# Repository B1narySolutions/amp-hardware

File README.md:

# Amp hardware

The circuit board for our capstone guitar amp, designed in KiCad 10.

The amp board (top, then bottom seen from below):

## The amp board

One 4-layer, 100 × 78 mm board, in `amp-board/`. It holds the Daisy Seed3 that does the audio processing, the guitar and
AUX inputs, an I2C headphone amp (TPA6130A2), the battery input, the 5 V distribution and the class D speaker amp
(TPA3118D2). The Daisy stands upright in the middle and divides the board: audio on its left and in front of it, the
battery entry and class D amp on its right, all over a solid ground plane. The 5 V buck stays off the board. JLCPCB
assembles the surface-mount parts; the rest is soldered by hand from a DigiKey order.

Status: laid out, not ordered. `amp-board/DESIGN.md` lists what is still open.

## Where to look

- `amp-board/DESIGN.md`: how the board works and why, the decisions made, and what is still open
- `amp-board/TEST_PLAN.md`: bring-up and test steps
- `amp-board/amp-board.kicad_pro`: the KiCad project. Part numbers (DigiKey, LCSC) are fields on the schematic's
  parts; the order files are generated from them into `amp-board/fab/`, which git ignores
- Each ordered revision is a git tag (`amp-board-v1`, ...) with its Gerbers, assembly files and DigiKey order attached
  to the GitHub release

## Legacy boards

`legacy/` holds the two boards the amp board grew out of, kept as they were ordered on 2026-11-05: the audio board rev 2
(`legacy/audio-board/`, 2-layer, hand-soldered) and the power board rev 1 (`legacy/power-board/`), joined by screw
terminals and wires. `legacy/README.md` lists their files. They are no longer developed.

## Opening the design

Open `amp-board/amp-board.kicad_pro` with KiCad 10. The board's own footprints, symbols and 3D models are in
`amp-board/lib/`, and the library tables point to them, so no setup is needed.

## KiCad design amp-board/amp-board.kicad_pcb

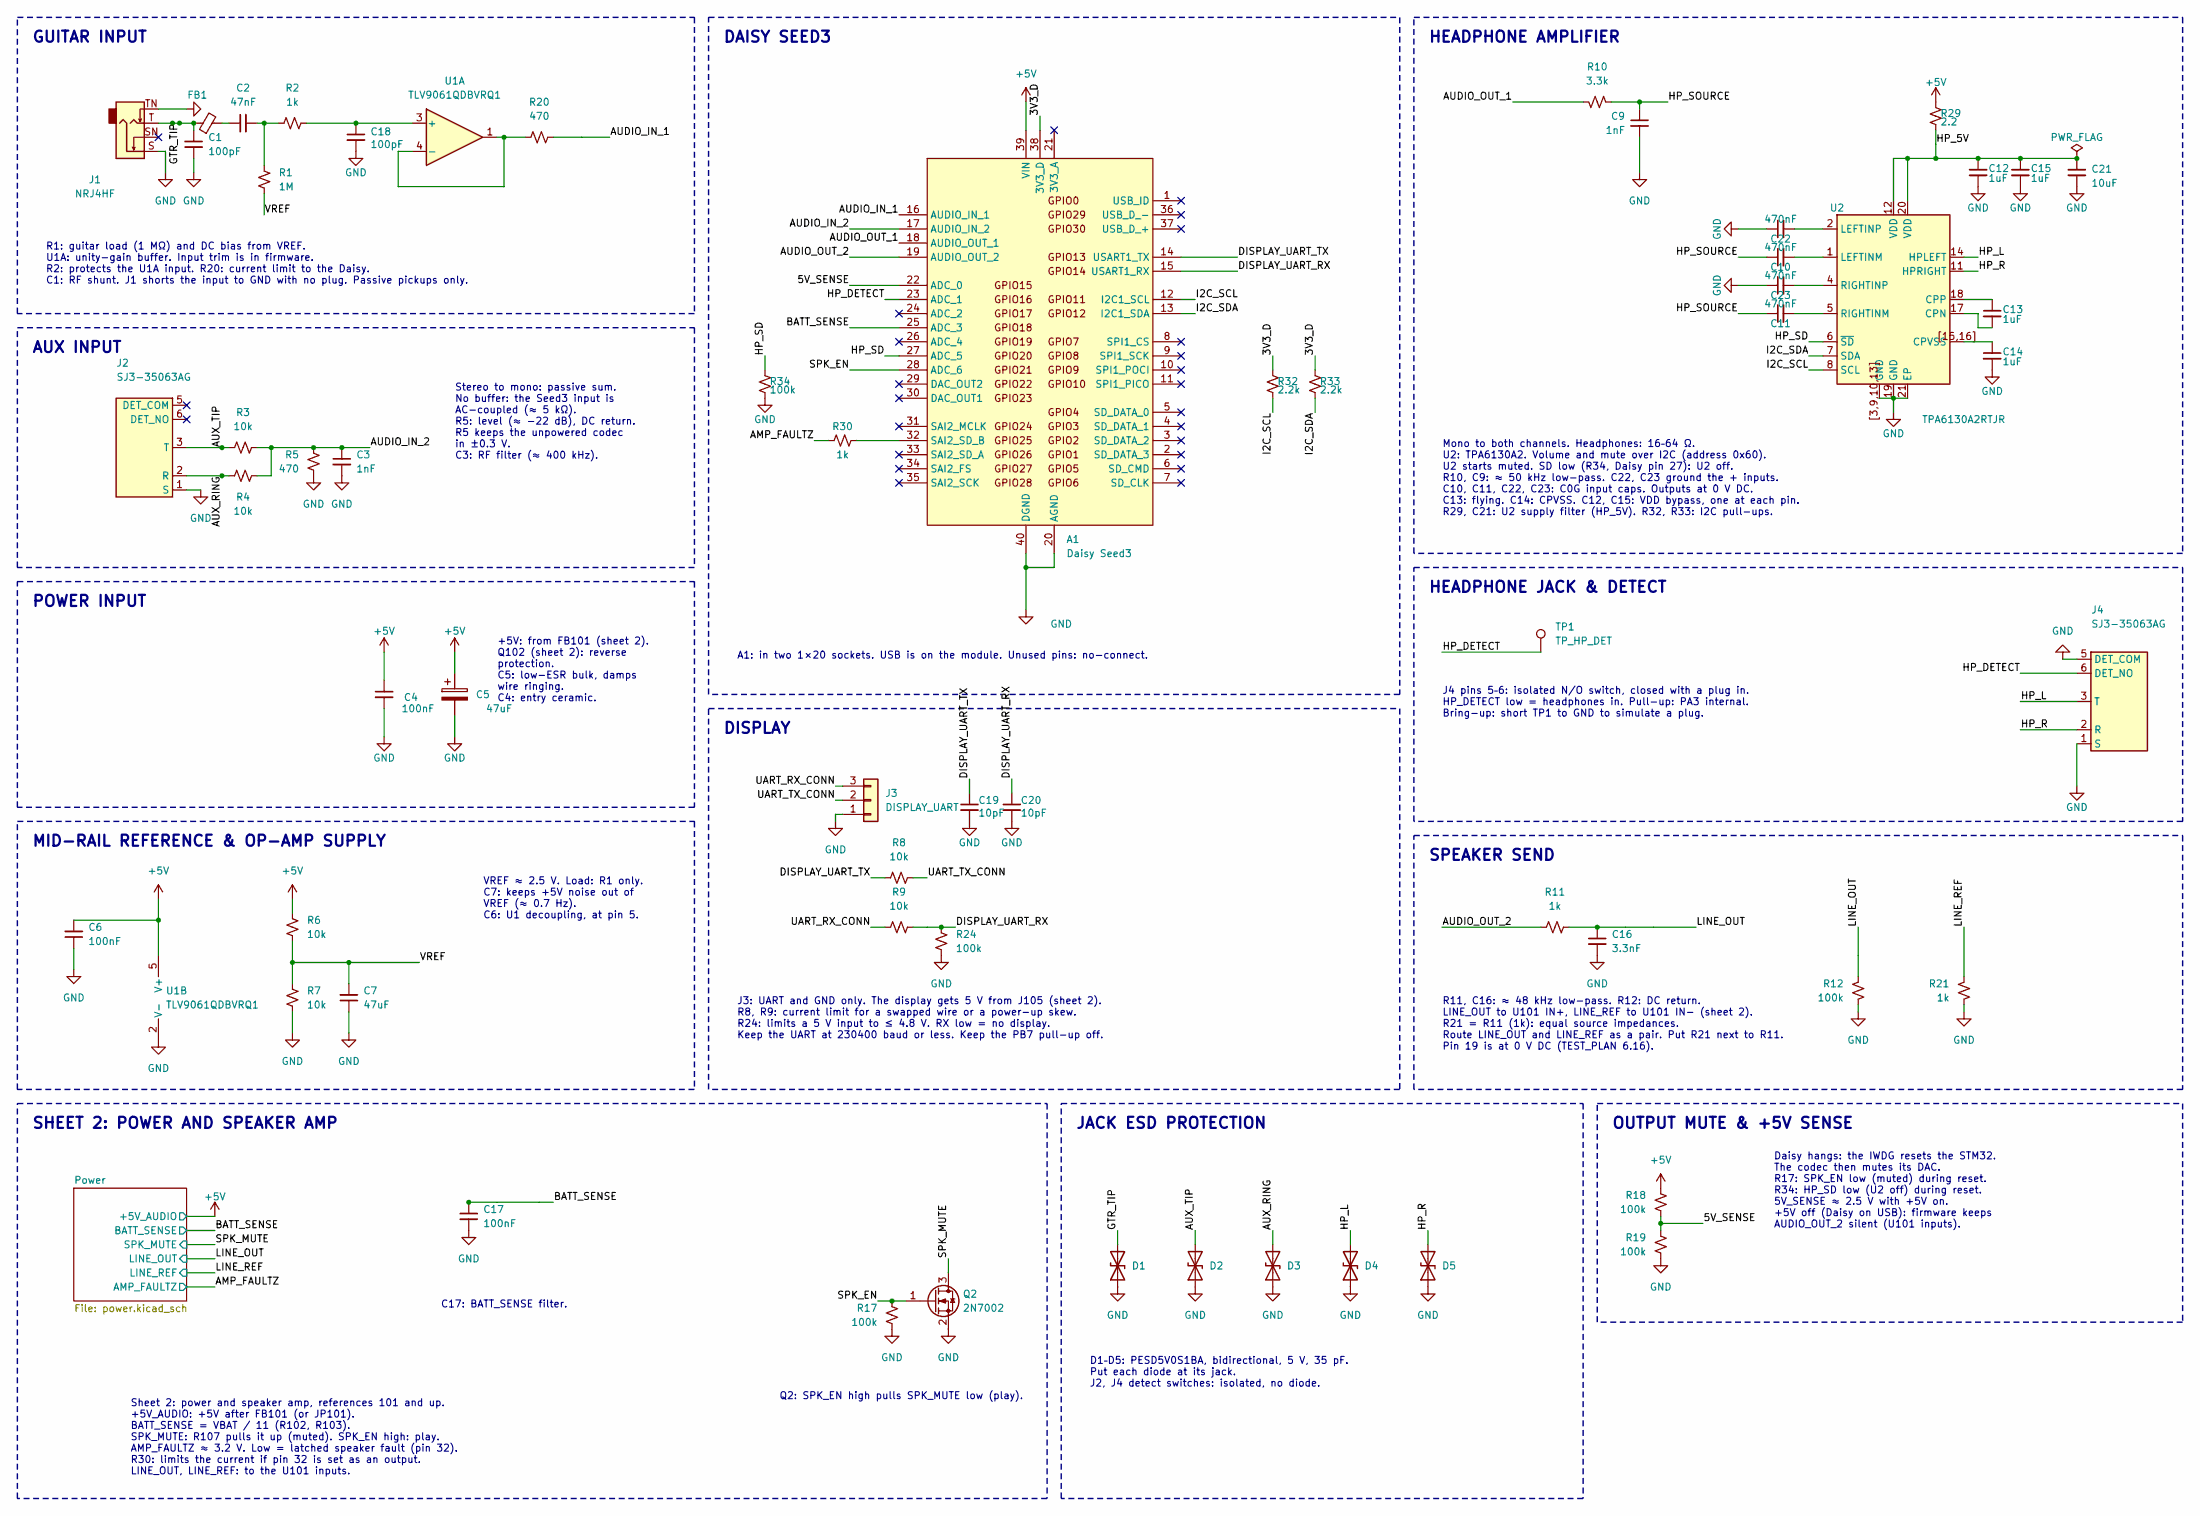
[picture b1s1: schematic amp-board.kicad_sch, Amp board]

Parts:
A1: Daisy Seed3; Electrosmith_Daisy_Seed
C1, C18: 100pF; C_0603_1608Metric; Voltage 50V; MPN CL10C101JB8NNNC; DigiKey 1276-1008-1-ND
C2: 47nF; C_0805_2012Metric; Voltage 25V; MPN C0805C473J3GACTU; DigiKey 399-C0805C473J3GACTUCT-ND
C3, C9: 1nF; C_0603_1608Metric; Voltage 50V; MPN CL10C102JB8NNNC; DigiKey 1276-1091-1-ND
C4, C6, C17: 100nF; C_0603_1608Metric; Voltage 50V; MPN C0603C104K5RACTU; DigiKey 399-C0603C104K5RACTUCT-ND
C5: 47uF; CP_Radial_D5.0mm_P2.00mm; Voltage 16V; MPN 860010472005; DigiKey 732-8628-1-ND
C7: 47uF; C_1210_3225Metric; Voltage 16V; MPN GRM32ER61C476KE15L; DigiKey 490-6539-1-ND
C10, C11, C22, C23: 470nF; C_1206_3216Metric; Voltage 25V; MPN GRM31C5C1E474JE01L; DigiKey 490-GRM31C5C1E474JE01LCT-ND
C12, C13, C14, C15: 1uF; C_0805_2012Metric; Voltage 50V; MPN C0805C105K5RACTU; DigiKey 399-C0805C105K5RACTUCT-ND
C16: 3.3nF; C_0603_1608Metric; Voltage 50V; MPN C0603C332J5GACTU; DigiKey 399-C0603C332J5GACTUCT-ND
C19, C20: 10pF; C_0603_1608Metric; Voltage 50V; MPN CL10C100JB8NNNC; DigiKey 1276-1027-1-ND
C21: 10uF; C_0805_2012Metric; Voltage 16V; MPN KGM21AR71C106KU; DigiKey 478-KGM21AR71C106KUCT-ND
D1, D2, D3, D4, D5: PESD5V0S1BA; D_SOD-323; MPN PESD5V0S1BAF; DigiKey 1727-PESD5V0S1BAFCT-ND
FB1: 600R GHz; L_0603_1608Metric; MPN BLM18HG601SN1D; DigiKey 490-1033-1-ND
J1: NRJ4HF; Jack_6.35mm_Neutrik_NRJ4HF_Horizontal; MPN NRJ4HF; DigiKey 6473-NRJ4HF-ND
J2, J4: SJ3-35063AG; Jack_3.5mm_SameSky_SJ3-35063AG_Horizontal; MPN SJ3-35063AG; DigiKey 2223-SJ3-35063AG-ND
J3: DISPLAY_UART; TerminalBlock_Phoenix_PT-1,5-3-3.5-H_1x03_P3.50mm_Horizontal; MPN 1984620; DigiKey 277-1722-ND
Q2: 2N7002; SOT-23; MPN 2N7002NXAKR; DigiKey 1727-8643-1-ND
R1: 1M; R_0603_1608Metric; MPN RC0603FR-071ML; DigiKey 311-1.00MHRCT-ND
R2, R11, R21, R30: 1k; R_0603_1608Metric; MPN RC0603FR-071KL; DigiKey 311-1.00KHRCT-ND
R3, R4, R6, R7, R8, R9: 10k; R_0603_1608Metric; MPN RMCF0603FT10K0; DigiKey RMCF0603FT10K0CT-ND
R5, R20: 470; R_0603_1608Metric; MPN RC0603FR-07470RL; DigiKey 311-470HRCT-ND
R10: 3.3k; R_0603_1608Metric; MPN RC0603FR-073K3L; DigiKey 311-3.30KHRCT-ND
R12, R17, R18, R19, R24, R34: 100k; R_0603_1608Metric; MPN RMCF0603FT100K; DigiKey RMCF0603FT100KCT-ND
R29: 2.2; R_0603_1608Metric; MPN RMCF0603FT2R20; DigiKey RMCF0603FT2R20CT-ND
R32, R33: 2.2k; R_0603_1608Metric; MPN RC0603FR-072K2L; DigiKey 311-2.20KHRCT-ND
TP1: TP_HP_DET; TestPoint_Pad_D2.0mm
U1: TLV9061QDBVRQ1; SOT-23-5; MPN TLV9061QDBVRQ1; DigiKey 296-TLV9061QDBVRQ1CT-ND
U2: TPA6130A2RTJR; WQFN-20-1EP_4x4mm_P0.5mm_EP2.7x2.7mm; MPN TPA6130A2RTJR; DigiKey 296-21656-1-ND

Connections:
+5V: A1.39 (VIN), C4.1, C5.1, C6.2, R6.1, R18.1, R29.1, U1.5 (V+); also elsewhere on the board
/3V3_D: A1.38 (3V3_D), R32.1, R33.1
/5V_SENSE: A1.22 (ADC_0), R18.2, R19.1
/AMP_FAULTZ: R30.1; also elsewhere on the board
/AUDIO_IN_1: A1.16 (AUDIO_IN_1), R20.2
/AUDIO_IN_2: A1.17 (AUDIO_IN_2), C3.1, R3.2, R4.2, R5.1
/AUDIO_OUT_1: A1.18 (AUDIO_OUT_1), R10.2
/AUDIO_OUT_2: A1.19 (AUDIO_OUT_2), R11.1
/AUX_RING: D3.2 (A2), J2.2 (R), R4.1
/AUX_TIP: D2.2 (A2), J2.3 (T), R3.1
/BATT_SENSE: A1.25 (ADC_3), C17.1; also elsewhere on the board
/DISPLAY_UART_RX: A1.15 (USART1_RX), C20.1, R9.2, R24.1
/DISPLAY_UART_TX: A1.14 (USART1_TX), C19.1, R8.1
/GTR_TIP: C1.1, D1.2 (A2), FB1.1, J1.T
/HP_5V: C12.1, C15.1, C21.1, R29.2, U2.12 (VDD), U2.20 (VDD)
/HP_DETECT: A1.23 (ADC_1), J4.6 (DET_NO), TP1.1 (1_1)
/HP_L: D4.2 (A2), J4.3 (T), U2.14 (HPLEFT)
/HP_R: D5.2 (A2), J4.2 (R), U2.11 (HPRIGHT)
/HP_SD: A1.27 (ADC_5), R34.1, U2.6 (~SD)
/HP_SOURCE: C9.1, C10.1, C11.1, R10.1
/I2C_SCL: A1.12 (I2C1_SCL), R32.2, U2.8 (SCL)
/I2C_SDA: A1.13 (I2C1_SDA), R33.2, U2.7 (SDA)
/LINE_OUT: C16.1, R11.2, R12.2; also elsewhere on the board
/LINE_REF: R21.2; also elsewhere on the board
/SPK_EN: A1.28 (ADC_6), Q2.1 (G), R17.1
/SPK_MUTE: Q2.3 (D); also elsewhere on the board
/UART_RX_CONN: J3.3, R9.1
/UART_TX_CONN: J3.2, R8.2
/VREF: C7.2, R1.2, R6.2, R7.1
GND: A1.20 (AGND), A1.40 (DGND), C1.2, C3.2, C4.2, C5.2, C6.1, C7.1, C9.2, C12.2, C14.2, C15.2, C16.2, C17.2, C18.2, C19.2, C20.2, C21.2, C22.1, C23.1, D1.1 (A1), D2.1 (A1), D3.1 (A1), D4.1 (A1), D5.1 (A1), J1.S, J1.TN, J2.1 (S), J3.1, J4.1 (S), J4.5 (DET_COM), Q2.2 (S), R5.2, R7.2, R12.1, R17.2, R19.2, R21.1, R24.2, R34.2, U1.2 (V-), U2.3, U2.9, U2.10, U2.13, U2.19 (GND), U2.21 (EP), U2.[3,9,10,13] (GND); also elsewhere on the board
unnamed: A1.32 (SAI2_SD_B), R30.2
unnamed: C2.1, FB1.2
unnamed: C2.2, R1.1, R2.1
unnamed: C18.1, R2.2, U1.3 (+)
unnamed: R20.1, U1.1, U1.4 (-)
unnamed: C13.2, U2.17 (CPN)
unnamed: C13.1, U2.18 (CPP)
unnamed: C14.1, U2.15, U2.16, U2.[15,16] (CPVSS)
unnamed: C10.2, U2.1 (LEFTINM)
unnamed: C22.2, U2.2 (LEFTINP)
unnamed: C11.2, U2.5 (RIGHTINM)
unnamed: C23.2, U2.4 (RIGHTINP)

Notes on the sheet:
GUITAR INPUT
AUX INPUT
POWER INPUT
MID-RAIL REFERENCE & OP-AMP SUPPLY
DAISY SEED3
DISPLAY
HEADPHONE AMPLIFIER
HEADPHONE JACK & DETECT
SPEAKER SEND
SHEET 2: POWER AND SPEAKER AMP
OUTPUT MUTE & +5V SENSE
R1: guitar load (1 MΩ) and DC bias from VREF. U1A: unity-gain buffer. Input trim is in firmware. R2: protects the U1A input. R20: current limit to the Daisy. C1: RF shunt. J1 shorts the input to GND with no plug. Passive pickups only.
Stereo to mono: passive sum. No buffer: the Seed3 input is AC-coupled (≈ 5 kΩ). R5: level (≈ −22 dB), DC return. R5 keeps the unpowered codec in ±0.3 V. C3: RF filter (≈ 400 kHz).
+5V: from FB101 (sheet 2). Q102 (sheet 2): reverse protection. C5: low-ESR bulk, damps wire ringing. C4: entry ceramic.
VREF ≈ 2.5 V. Load: R1 only. C7: keeps +5V noise out of VREF (≈ 0.7 Hz). C6: U1 decoupling, at pin 5.
A1: in two 1×20 sockets. USB is on the module. Unused pins: no-connect.
J3: UART and GND only. The display gets 5 V from J105 (sheet 2). R8, R9: current limit for a swapped wire or a power-up skew. R24: limits a 5 V input to ≤ 4.8 V. RX low = no display. Keep the UART at 230400 baud or less. Keep the PB7 pull-up off.
Mono to both channels. Headphones: 16–64 Ω. U2: TPA6130A2. Volume and mute over I2C (address 0x60). U2 starts muted. SD low (R34, Daisy pin 27): U2 off. R10, C9: ≈ 50 kHz low-pass. C22, C23 ground the + inputs. C10, C11, C22, C23: C0G input caps. Outputs at 0 V DC. C13: flying. C14: CPVSS. C12, C15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
J4 pins 5–6: isolated N/O switch, closed with a plug in. HP_DETECT low = headphones in. Pull-up: PA3 internal. Bring-up: short TP1 to GND to simulate a plug.
R11, C16: ≈ 48 kHz low-pass. R12: DC return. LINE_OUT to U101 IN+, LINE_REF to U101 IN− (sheet 2). R21 = R11 (1k): equal source impedances. Route LINE_OUT and LINE_REF as a pair. Put R21 next to R11. Pin 19 is at 0 V DC (TEST_PLAN 6.16).
Sheet 2: power and speaker amp, references 101 and up. +5V_AUDIO: +5V after FB101 (or JP101). BATT_SENSE = VBAT / 11 (R102, R103). SPK_MUTE: R107 pulls it up (muted). SPK_EN high: play. AMP_FAULTZ ≈ 3.2 V. Low = latched speaker fault (pin 32). R30: limits the current if pin 32 is set as an output. 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
Daisy hangs: the IWDG resets the STM32. The codec then mutes its DAC. R17: SPK_EN low (muted) during reset. R34: HP_SD low (U2 off) during reset. 5V_SENSE ≈ 2.5 V with +5V on. +5V off (Daisy on USB): firmware keeps AUDIO_OUT_2 silent (U101 inputs).
JACK ESD PROTECTION
D1–D5: PESD5V0S1BA, bidirectional, 5 V, 35 pF. Put each diode at its jack. J2, J4 detect switches: isolated, no diode.
C17: BATT_SENSE filter.
Q2: SPK_EN high pulls SPK_MUTE low (play).

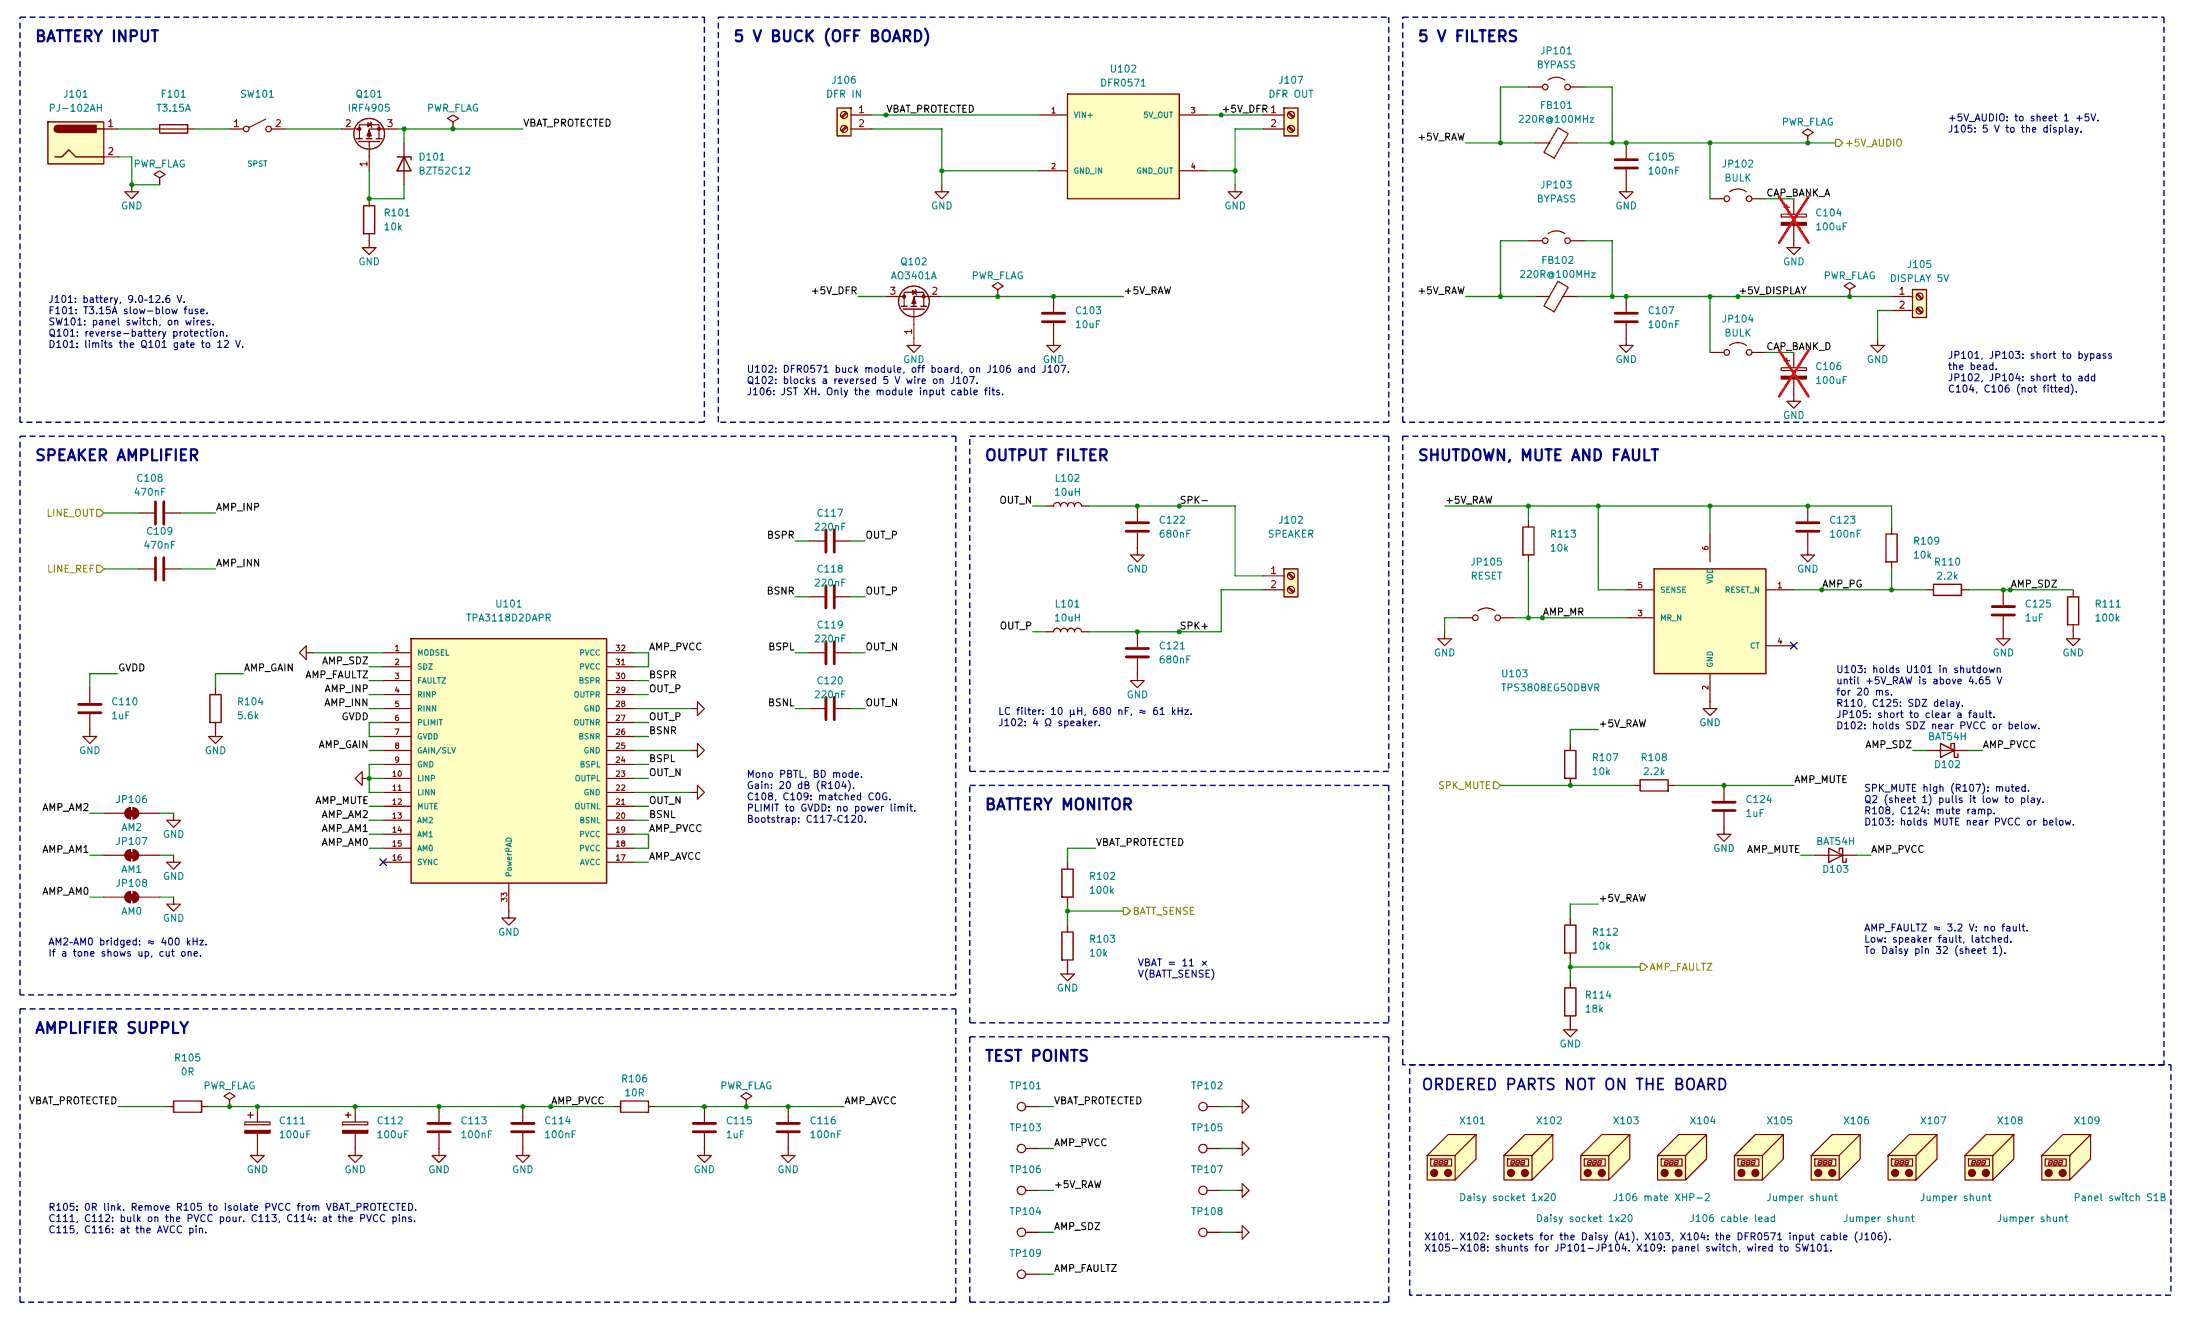
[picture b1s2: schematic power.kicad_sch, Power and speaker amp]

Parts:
C103: 10uF; C_0805_2012Metric; Voltage 16V; MPN KGM21AR71C106KU; DigiKey 478-KGM21AR71C106KUCT-ND
C104, C106: 100uF; CP_Radial_D6.3mm_P2.50mm; Voltage 25V; MPN EEU-FM1E101H; DigiKey 10-EEU-FM1E101HCT-ND; not fitted
C105, C107, C113, C114, C116, C123: 100nF; C_0603_1608Metric; Voltage 50V; MPN C0603C104K5RACTU; DigiKey 399-C0603C104K5RACTUCT-ND
C108, C109: 470nF; C_1206_3216Metric; Voltage 25V; MPN GRM31C5C1E474JE01L; DigiKey 490-GRM31C5C1E474JE01LCT-ND
C110, C115, C124, C125: 1uF; C_0805_2012Metric; Voltage 50V; MPN C0805C105K5RACTU; DigiKey 399-C0805C105K5RACTUCT-ND
C111, C112: 100uF; CP_Radial_D6.3mm_P2.50mm; Voltage 25V; MPN EEU-FM1E101H; DigiKey 10-EEU-FM1E101HCT-ND
C117, C118, C119, C120: 220nF; C_0603_1608Metric; Voltage 50V; MPN CL10B224KB8NNNC; DigiKey 1276-CL10B224KB8NNNCCT-ND
C121, C122: 680nF; C_0805_2012Metric; Voltage 50V; MPN C0805C684K5RACTU; DigiKey 399-C0805C684K5RACTUCT-ND
D101: BZT52C12; D_SOD-123; MPN BZT52C12-TP; LCSC C668891
D102, D103: BAT54H; D_SOD-323; MPN NSVBAT54HT1G; DigiKey NSVBAT54HT1GOSCT-ND
F101: T3.15A; Fuse_Bel_0683G_4818; MPN 0683G3150-01; DigiKey 5923-0683G3150-01CT-ND
FB101, FB102: 220R@100MHz; L_0603_1608Metric; MPN MPZ1608S221ATA00; LCSC C76815
J101: PJ-102AH; BarrelJack_CUI_PJ-102AH_Horizontal; MPN PJ-102AH; DigiKey CP-102AH-ND
J102: SPEAKER; TerminalBlock_Phoenix_PT-1,5-2-3.5-H_1x02_P3.50mm_Horizontal; MPN 1984617; DigiKey 277-1721-ND
J105: DISPLAY 5V; TerminalBlock_Phoenix_PT-1,5-2-3.5-H_1x02_P3.50mm_Horizontal; MPN 1984617; DigiKey 277-1721-ND
J106: DFR IN; JST_XH_S2B-XH-A_1x02_P2.50mm_Horizontal; MPN S2B-XH-A; DigiKey 455-S2B-XH-A-ND
J107: DFR OUT; TerminalBlock_Phoenix_PT-1,5-2-3.5-H_1x02_P3.50mm_Horizontal; MPN 1984617; DigiKey 277-1721-ND
JP101, JP103: BYPASS; PinHeader_1x02_P2.54mm_Vertical; MPN M20-9990245; DigiKey 952-2261-ND
JP102, JP104: BULK; PinHeader_1x02_P2.54mm_Vertical; MPN M20-9990245; DigiKey 952-2261-ND
JP105: RESET; PinHeader_1x02_P2.54mm_Vertical; MPN M20-9990245; DigiKey 952-2261-ND
JP106: AM2; SolderJumper-2_P1.3mm_Bridged_RoundedPad1.0x1.5mm
JP107: AM1; SolderJumper-2_P1.3mm_Bridged_RoundedPad1.0x1.5mm
JP108: AM0; SolderJumper-2_P1.3mm_Bridged_RoundedPad1.0x1.5mm
L101, L102: 10uH; L_Bourns_SRP1038A_LeadFrame; MPN SRP1038A-100M; LCSC C780184
Q101: IRF4905; TO-220-3_Vertical; MPN IRF4905PBF; DigiKey IRF4905PBF-ND
Q102: AO3401A; SOT-23; MPN AO3401A; DigiKey 785-1001-1-ND
R101, R103, R107, R109, R112, R113: 10k; R_0603_1608Metric; MPN RMCF0603FT10K0; DigiKey RMCF0603FT10K0CT-ND
R102, R111: 100k; R_0603_1608Metric; MPN RMCF0603FT100K; DigiKey RMCF0603FT100KCT-ND
R104: 5.6k; R_0603_1608Metric; MPN RC0603FR-075K6L; DigiKey 311-5.60KHRCT-ND
R105: 0R; R_2512_6332Metric; MPN RC2512JK-070RL; LCSC C189505
R106: 10R; R_0603_1608Metric; MPN RMCF0603FT10R0; DigiKey RMCF0603FT10R0CT-ND
R108, R110: 2.2k; R_0603_1608Metric; MPN RC0603FR-072K2L; DigiKey 311-2.20KHRCT-ND
R114: 18k; R_0603_1608Metric; MPN RMCF0603FT18K0; DigiKey RMCF0603FT18K0CT-ND
SW101: SPST; TerminalBlock_Phoenix_PT-1,5-2-3.5-H_1x02_P3.50mm_Horizontal; MPN 1984617; DigiKey 277-1721-ND
TP101: VBAT_PROTECTED; TestPoint_Pad_D2.0mm
TP102, TP105, TP107, TP108: GND; TestPoint_Pad_D2.0mm
TP103: AMP_PVCC; TestPoint_Pad_D2.0mm
TP104: AMP_SDZ; TestPoint_Pad_D2.0mm
TP106: +5V_RAW; TestPoint_Pad_D2.0mm
TP109: AMP_FAULTZ; TestPoint_Pad_D2.0mm
U101: TPA3118D2DAPR; TI_DAP0032C_HTSSOP32_P0.65mm_EP3.04x3.74mm; MPN TPA3118D2DAPR; LCSC C46497
U102: DFR0571; MPN DFR0571; DigiKey 1738-1442-ND
U103: TPS3808EG50DBVR; SOT-23-6; MPN TPS3808EG50DBVR; LCSC C30139374
X101, X102: Daisy socket 1x20; MPN PPTC201LFBN-RC; DigiKey S7018-ND
X103: J106 mate XHP-2; MPN XHP-2; DigiKey 455-2266-ND
X104: J106 cable lead; MPN ASXHSXH22K305; DigiKey 455-3241-ND
X105, X106, X107, X108: Jumper shunt; MPN M7567-05; DigiKey 952-2171-ND
X109: Panel switch S1B; MPN S1B; DigiKey 6281-S1B-ND

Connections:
+5V: C105.1, FB101.2, JP101.2 (B), JP102.1 (A); also elsewhere on the board
/AMP_FAULTZ: R112.2, R114.1, TP109.1, U101.3 (FAULTZ); also elsewhere on the board
/BATT_SENSE: R102.2, R103.1; also elsewhere on the board
/LINE_OUT: C108.1; also elsewhere on the board
/LINE_REF: C109.1; also elsewhere on the board
/Power/+5V_DFR: J107.1, Q102.3 (D), U102.3 (5V_OUT)
/Power/+5V_DISPLAY: C107.1, FB102.2, J105.1, JP103.2 (B), JP104.1 (A)
/Power/+5V_RAW: C103.1, C123.1, FB101.1, FB102.1, JP101.1 (A), JP103.1 (A), Q102.2 (S), R107.1, R109.1, R112.1, R113.1, TP106.1, U103.5 (SENSE), U103.6 (VDD)
/Power/AMP_AM0: JP108.1 (A), U101.15 (AM0)
/Power/AMP_AM1: JP107.1 (A), U101.14 (AM1)
/Power/AMP_AM2: JP106.1 (A), U101.13 (AM2)
/Power/AMP_AVCC: C115.1, C116.1, R106.2, U101.17 (AVCC)
/Power/AMP_GAIN: R104.1, U101.8 (GAIN/SLV)
/Power/AMP_INN: C109.2, U101.5 (RINN)
/Power/AMP_INP: C108.2, U101.4 (RINP)
/Power/AMP_MR: JP105.1 (A), R113.2, U103.3 (MR_N)
/Power/AMP_MUTE: C124.1, D103.2 (A), R108.2, U101.12 (MUTE)
/Power/AMP_PG: R109.2, R110.1, U103.1 (RESET_N)
/Power/AMP_PVCC: C111.1, C112.1, C113.1, C114.1, D102.1 (K), D103.1 (K), R105.2, R106.1, TP103.1, U101.18 (PVCC), U101.19 (PVCC), U101.31 (PVCC), U101.32 (PVCC)
/Power/AMP_SDZ: C125.1, D102.2 (A), R110.2, R111.1, TP104.1, U101.2 (SDZ)
/Power/BSNL: C120.1, U101.20 (BSNL)
/Power/BSNR: C118.1, U101.26 (BSNR)
/Power/BSPL: C119.1, U101.24 (BSPL)
/Power/BSPR: C117.1, U101.30 (BSPR)
/Power/CAP_BANK_A: C104.1, JP102.2 (B)
/Power/CAP_BANK_D: C106.1, JP104.2 (B)
/Power/GVDD: C110.1, U101.6 (PLIMIT), U101.7 (GVDD)
/Power/OUT_N: C119.2, C120.2, L102.1, U101.21 (OUTNL), U101.23 (OUTPL)
/Power/OUT_P: C117.2, C118.2, L101.1, U101.27 (OUTNR), U101.29 (OUTPR)
/Power/SPK+: C121.1, J102.2, L101.2
/Power/SPK-: C122.1, J102.1, L102.2
/Power/VBAT_PROTECTED: D101.1 (K), J106.1, Q101.3 (S), R102.1, R105.1, TP101.1, U102.1 (VIN+)
/SPK_MUTE: R107.2, R108.1; also elsewhere on the board
GND: C103.2, C104.2, C105.2, C106.2, C107.2, C110.2, C111.2, C112.2, C113.2, C114.2, C115.2, C116.2, C121.2, C122.2, C123.2, C124.2, C125.2, J101.2, J105.2, J106.2, J107.2, JP105.2 (B), JP106.2 (B), JP107.2 (B), JP108.2 (B), Q102.1 (G), R101.2, R103.2, R104.2, R111.2, R114.2, TP102.1, TP105.1, TP107.1, TP108.1, U101.1 (MODSEL), U101.9 (GND), U101.10 (LINP), U101.11 (LINN), U101.22 (GND), U101.25 (GND), U101.28 (GND), U101.33 (PowerPAD), U102.2 (GND_IN), U102.4 (GND_OUT), U103.2 (GND); also elsewhere on the board
unnamed: D101.2 (A), Q101.1 (G), R101.1
unnamed: F101.1, J101.1
unnamed: Q101.2 (D), SW101.2 (B)
unnamed: F101.2, SW101.1 (A)

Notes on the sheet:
BATTERY INPUT
J101: battery, 9.0–12.6 V. F101: T3.15A slow-blow fuse. SW101: panel switch, on wires. Q101: reverse-battery protection. D101: limits the Q101 gate to 12 V.
5 V BUCK (OFF BOARD)
U102: DFR0571 buck module, off board, on J106 and J107. Q102: blocks a reversed 5 V wire on J107. J106: JST XH. Only the module input cable fits.
5 V FILTERS
+5V_AUDIO: to sheet 1 +5V. J105: 5 V to the display.
JP101, JP103: short to bypass the bead. JP102, JP104: short to add C104, C106 (not fitted).
SPEAKER AMPLIFIER
AM2–AM0 bridged: ≈ 400 kHz. If a tone shows up, cut one.
Mono PBTL, BD mode. Gain: 20 dB (R104). C108, C109: matched C0G. PLIMIT to GVDD: no power limit. Bootstrap: C117–C120.
AMPLIFIER SUPPLY
R105: 0R link. Remove R105 to isolate PVCC from VBAT_PROTECTED. C111, C112: bulk on the PVCC pour. C113, C114: at the PVCC pins. C115, C116: at the AVCC pin.
OUTPUT FILTER
LC filter: 10 µH, 680 nF, ≈ 61 kHz. J102: 4 Ω speaker.
BATTERY MONITOR
VBAT = 11 × V(BATT_SENSE)
TEST POINTS
SHUTDOWN, MUTE AND FAULT
U103: holds U101 in shutdown until +5V_RAW is above 4.65 V for 20 ms. R110, C125: SDZ delay. JP105: short to clear a fault. D102: holds SDZ near PVCC or below.
SPK_MUTE high (R107): muted. Q2 (sheet 1) pulls it low to play. R108, C124: mute ramp. D103: holds MUTE near PVCC or below.
AMP_FAULTZ ≈ 3.2 V: no fault. Low: speaker fault, latched. To Daisy pin 32 (sheet 1).
ORDERED PARTS NOT ON THE BOARD
X101, X102: sockets for the Daisy (A1). X103, X104: the DFR0571 input cable (J106). X105-X108: shunts for JP101-JP104. X109: panel switch, wired to SW101.

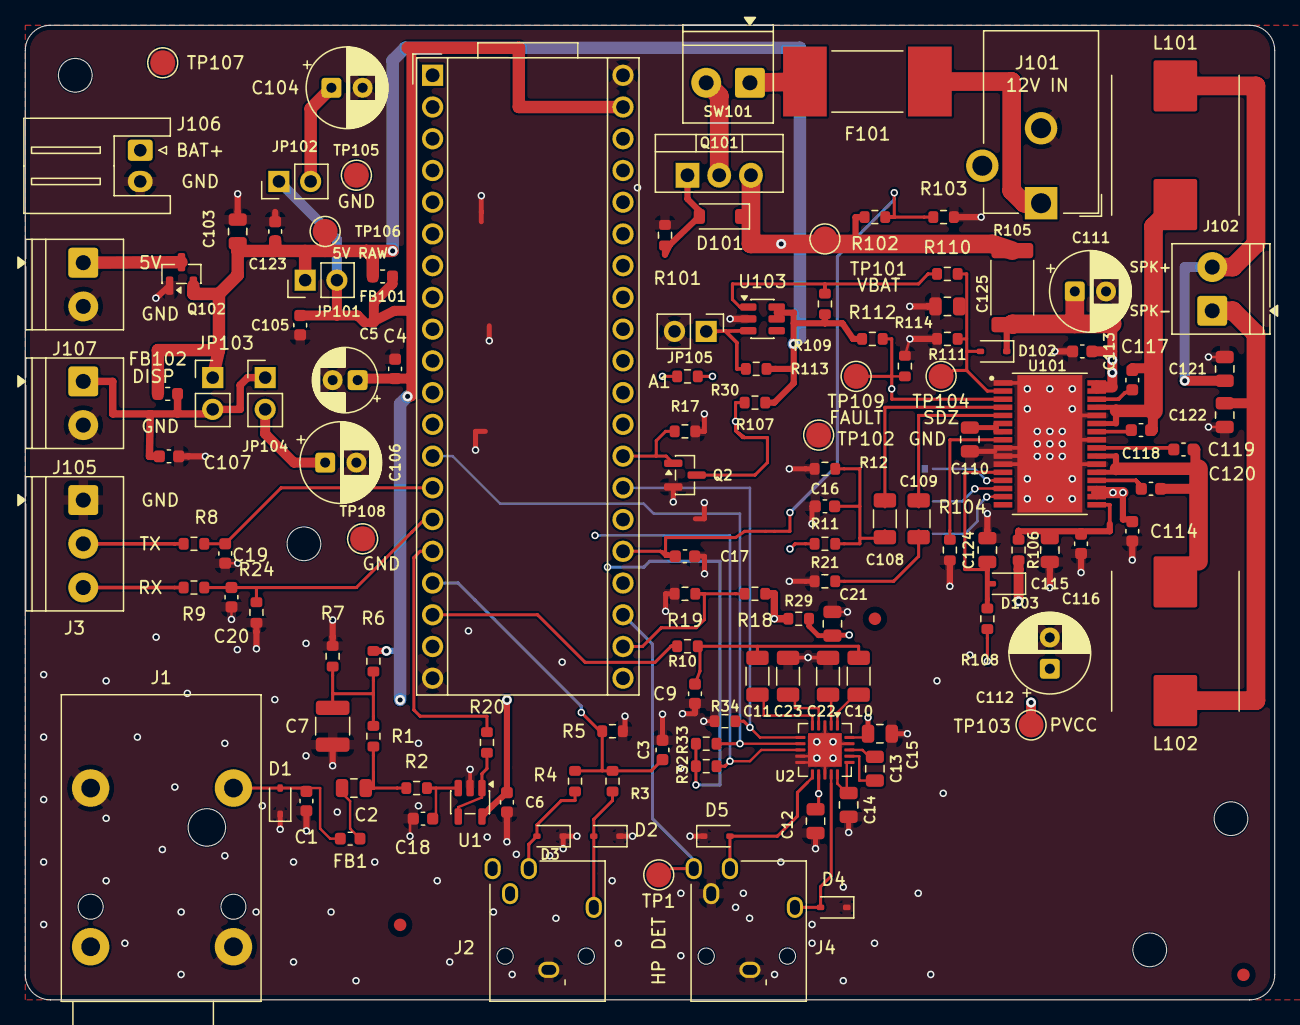
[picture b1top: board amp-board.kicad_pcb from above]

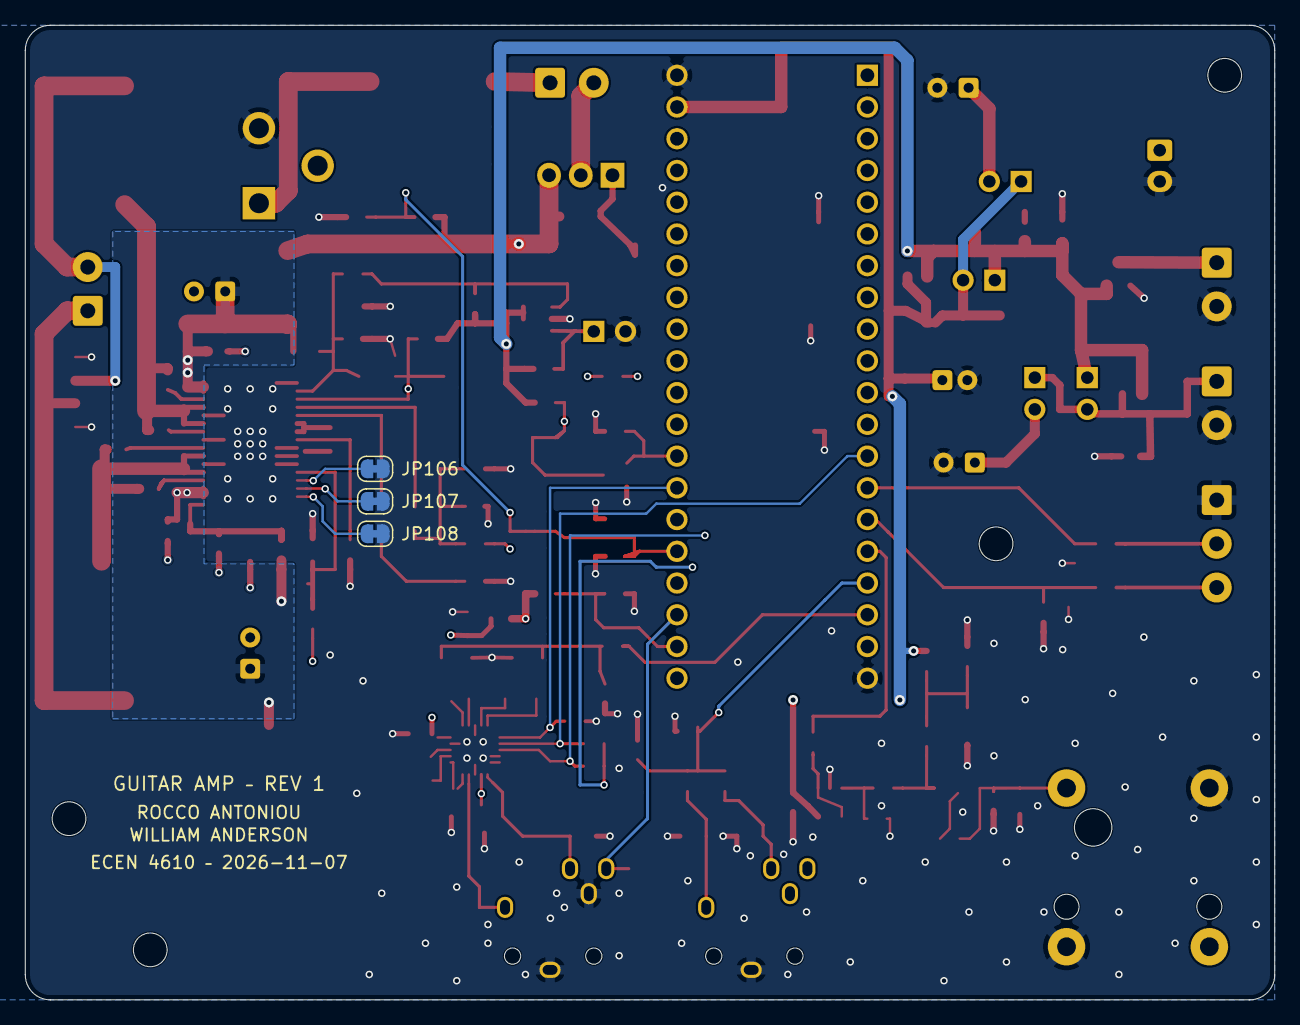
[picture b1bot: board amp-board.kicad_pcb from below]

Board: 4 copper layers, 100.0 x 78.0 mm, 139 parts (3 on the bottom side), 73 nets.

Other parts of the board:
FID1, FID2, FID3: Fiducial; Fiducial_1mm_Mask2mm
H1, H2, H3, H4: MountingHole_2.7mm_M2.5
